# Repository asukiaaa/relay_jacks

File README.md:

# relay_jacks

A KiCad pcb project for jacks controlled by relay.

[mpu9250-25mm-belt-holder](https://github.com/asukiaaa/mpu9250-25mm-belt-holder) is used for a sensor case.

# Components

- [Relay](http://akizukidenshi.com/catalog/g/gP-01346/)
- [Mosfet](http://akizukidenshi.com/catalog/g/gI-04256/)
- [Diode](http://akizukidenshi.com/catalog/g/gI-06467/)
- [Resistor 1k](http://akizukidenshi.com/catalog/g/gR-06102/)
- [3.5mm audio jack](http://akizukidenshi.com/catalog/g/gC-02460/)
- [LED Green](http://akizukidenshi.com/catalog/g/gI-06417/)
- [LED Yellow](http://akizukidenshi.com/catalog/g/gI-03984/)
- [LED Red](http://akizukidenshi.com/catalog/g/gI-03978/)

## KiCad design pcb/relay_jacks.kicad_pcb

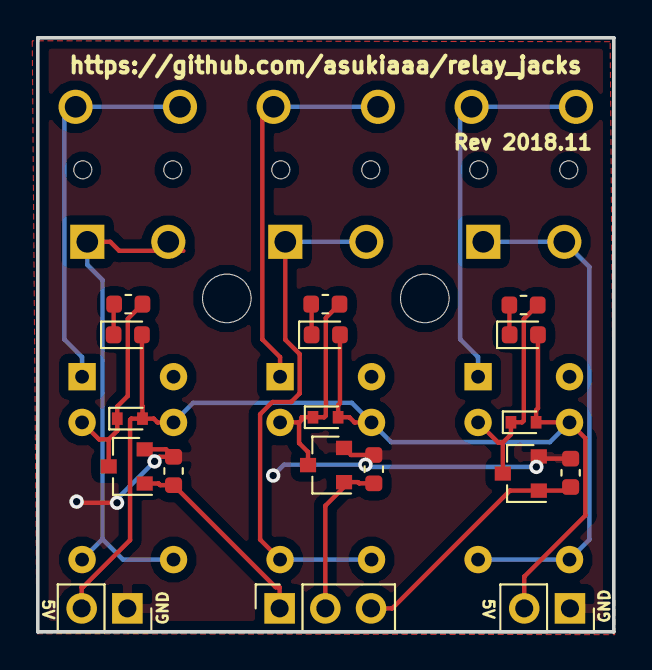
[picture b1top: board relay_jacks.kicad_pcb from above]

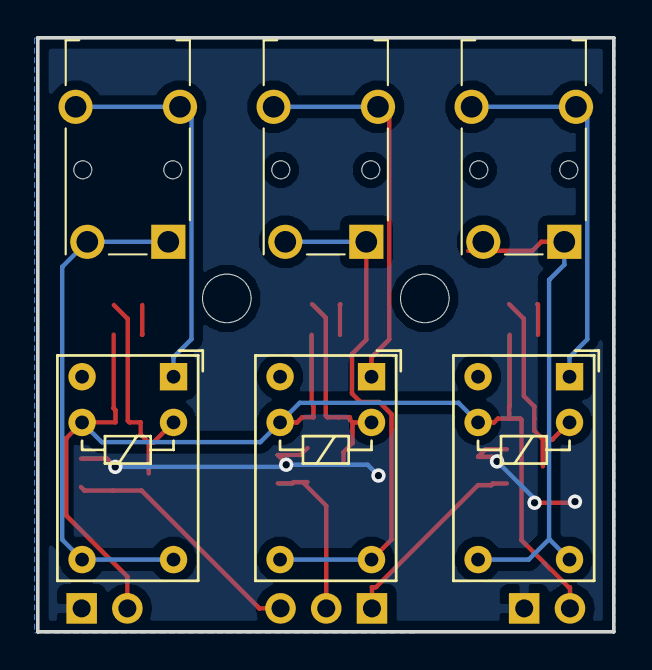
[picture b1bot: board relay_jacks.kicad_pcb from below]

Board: 2 copper layers, 32.0 x 33.0 mm, 26 parts (6 on the bottom side), 17 nets.

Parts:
D1, D3, D5: LED; LED_0603_1608Metric
D2, D4, D6: DIODE; D_SOD-523
J1, J5, J6: AudioJack3_Ground; Jack_3.5mm_Switronic_ST-005-G_horizontal
J2: Conn_01x03; PinSocket_1x03_P2.54mm_Vertical
J3, J4: Conn_01x02; PinSocket_1x02_P2.54mm_Vertical
K1, K2, K3: Y14x-1C-xxDS; Relay_SPDT_HsinDa_Y14
Q1, Q2, Q3: Q_NMOS_GSD; SOT-23
R1, R2, R3, R4, R5, R6: 1k; R_0603_1608Metric
REF1, REF2: MountingHole_2.7mm_M2.5_DIN965

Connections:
+5V: D1.2, D2.2, D3.2, D4.2, D5.2, D6.2, J3.2, J4.2, K1.4, K2.4, K3.4
GND: J3.1, J4.1, Q1.2, Q2.2, Q3.2, R2.2, R3.2, R5.2
unnamed: D1.1, R1.2
unnamed: D2.1, K1.3, Q1.3, R1.1
unnamed: D3.1, R4.2
unnamed: D4.1, K2.3, Q2.3, R4.1
unnamed: D5.1, R6.2
unnamed: D6.1, K3.3, Q3.3, R6.1
unnamed: J1.2, J1.3, K1.5, K1.6
unnamed: J1.4, K1.1
unnamed: J5.2, J5.3, K2.5, K2.6
unnamed: J5.4, K2.1
unnamed: J6.2, J6.3, K3.5, K3.6
unnamed: J6.4, K3.1
SIG0: J2.1, Q1.1, R2.1
SIG1: J2.2, Q2.1, R3.1
SIG2: J2.3, Q3.1, R5.1

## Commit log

2018-11-07 Create pcb directory
2018-11-07 Export partial model for testing
2018-11-07 Adjust case size with referencing test result
2018-11-09 Add a hole for wire
2018-11-09 Update cover design for new pcb
2018-11-15 Add pillow to fix wire to body of case
2018-11-16 Add cover
2018-11-16 Export stl for testing
2018-11-18 Update clearance of cover and hook hole
2018-11-18 Correct clearance from clealance
2018-11-18 Change number, position and hole style for mounting holes
2018-11-19 Remove cover for pro micro holder
2018-11-19 Correct pcb hole position
2018-11-19 Update mountingHoleRadius as 2.0 / 2mm for M2 screw
2018-11-19 Remove redundant clearance for usbHolePosition
2018-11-19 Add chamfer for usb and wire hole connection
2018-11-19 Update stl for testing
2018-11-21 Expand clealance for hook
2018-11-21 Change clealance between promicro and holder
2018-11-21 Update body stl file
2018-11-22 Use normal clearance for cover length
2018-11-22 Add chamfer again between usb and wire holes
2018-11-22 Update stl files
2018-11-22 Add *.pyc to case/.gitignore
2018-11-23 Change mouting hole size smaller as 1.8mm from 2.0mm
2018-11-23 Set moutingHoleBaseLength as 2.0mm
2018-11-23 Add a svg file as a stensil mask
2018-11-24 Rename wire as sensorWire
2018-11-24 Add relayWireSpace
2018-11-24 Change audioHoleRadius smaller
2018-11-24 Increase number of cover hooks
2018-11-24 Remove clearance from proMicroHolder
2018-11-24 Change shape of coverMoutHoleBase as square
2018-11-24 Change style of coverMountHoleBase
2018-11-24 Change y of relaysPcbHolePositions
2018-11-25 Remove holeClearance
2018-11-25 Add clearance between proMicroHoder and cover
2018-11-25 Add top left base
2018-11-28 Change size of relayWireSpace
2018-11-29 Add avr program
2018-11-29 Add side space for wire
2018-11-30 Export stl as full size
2018-11-30 Add images
2018-11-30 Add link of mpu9250 case
